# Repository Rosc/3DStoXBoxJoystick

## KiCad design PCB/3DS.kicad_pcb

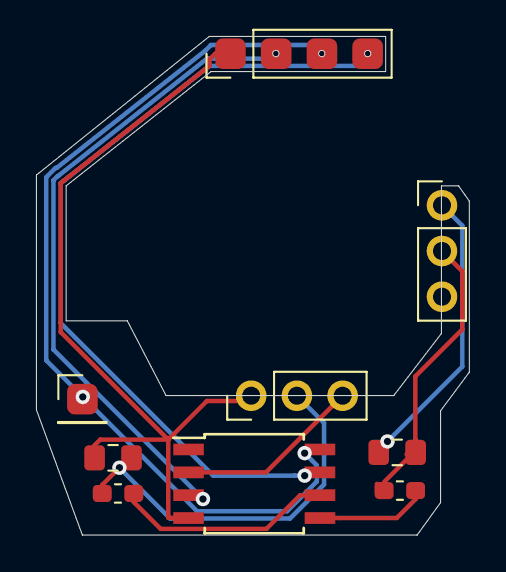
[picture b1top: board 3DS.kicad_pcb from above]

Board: 2 copper layers, 24.0 x 27.7 mm, 6 parts (0 on the bottom side), 6 nets.

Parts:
C1, C2: 10uf; C_0805_2012Metric_Pad1.15x1.40mm_HandSolder
R1, R2: 1k; R_0603_1608Metric_Pad1.05x0.95mm_HandSolder
U1: ATtiny45V-10SU; SOIJ-8_5.3x5.3mm_P1.27mm
\: PinHeader_1x01_P2.54mm_Vertical

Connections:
+3V3: U1.8, \.1
GND: C1.2, C2.2, U1.4
unnamed: R1.2, U1.5
unnamed: R2.2, U1.6
XOut: C2.1, R2.1
YOut: C1.1, R1.1

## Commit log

2020-03-15 Initial commit of the v2 flex cable assembly
2020-03-15 Moved from flex PCB to a roughed-out fiberglass PCB
2020-03-15 Debug firmware added
